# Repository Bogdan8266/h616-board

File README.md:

# Nebula Board (Allwinner H616 Devboard)

A compact, battery-powered 64-bit ARM development board measuring **50 mm × 50 mm** based on the **Allwinner H616** Quad-Core Cortex-A53 SoC with integrated powerbank PMU, high-speed DDR3, eMMC 5.1, and dual-band Wi-Fi.

Unlike standard commercial H616 boards (Orange Pi, Banana Pi, etc.) that require a 5V/3A wall adapter and shut down the moment you unplug the cable, **Nebula Board** features an onboard bidirectional fast-charging system that runs from a single Li-ion cell (18650 / Li-Po) and recharges via USB-C with USB-PD / QC4+.

---

##  Board Layout & Architecture

The PCB has been floorplanned to strictly separate high-speed digital buses, power conversion, and radio frequency:

* **Top-Right:** **Allwinner H616 SoC** (TFBGA284, 0.65 mm ball pitch).
* **Top-Center:** **DDR3 SDRAM** (BGA-96) — routed horizontally directly into H616 with ~15 mm trace lengths for minimal skew.
* **Bottom-Right:** **eMMC 5.1 Storage** (BGA-153) — routed vertically directly into the SoC for high-speed HS400 mode without crossing the DDR bus.
* **Bottom-Right Corner:** **Micro-HDMI (J2)** — 100 Ω impedance-matched TMDS differential pairs routed cleanly along the board edge.
* **Bottom-Center:** **AXP305 PMIC** — central multi-channel power distribution with 5 dedicated buck inductors (VDD_CPU, VDD_GPU, VCC_DRAM, etc.).
* **Bottom-Left:** **SW6206 Powerbank Controller** — handles 18W–22.5W fast charging, 1S battery fuel gauge, and system power boost.
* **Top-Left:** **Ampak AP6256 / Dual-Band Wi-Fi (2.4G / 5GHz + BT 5.0)** module with external **IPEX/U.FL** antenna connector.
* **Top Edge:** Standard **40-pin GPIO header** (including hardware **I2S3** audio lines and **I2C0**).
* **Bottom Edge:** **Dual USB-C ports** — isolated power and data paths.

---

##  JLCPCB 8-Layer Stackup & Impedance

The board is designed around JLCPCB's standard 8-layer stackup **`JLC08101H-1080`** with a finished thickness of **1.02 mm ±10%**.

### Layer Stackup Structure

* **L1 (F.Cu):** High-speed signals, RF 50 Ω, components (1 oz copper, 0.035 mm)
* **L2 (In1.Cu):** **Continuous Ground Plane (GND)** (0.5 oz copper, 0.0152 mm)
* **L3 (In2.Cu):** Inner signal routing — DDR3 striplines (0.5 oz copper, 0.0152 mm)
* **L4 (In3.Cu):** Ground / Power Plane (0.5 oz copper, 0.0152 mm)
* **L5 (In4.Cu):** Power Planes (VDD_CPU, VDD_GPU, +5V, +3.3V) (0.5 oz copper, 0.0152 mm)
* **L6 (In5.Cu):** Inner signal routing (0.5 oz copper, 0.0152 mm)
* **L7 (In6.Cu):** **Continuous Ground Plane (GND)** (0.5 oz copper, 0.0152 mm)
* **L8 (B.Cu):** Decoupling capacitors (0402 directly under BGA balls) & connectors (1 oz copper, 0.035 mm)

### Controlled Impedance Table

| Signal Group | Impedance | Layer | Trace Width | Spacing | Notes |
|:---|:---:|:---:|:---:|:---:|:---|
| **RF / Single-Ended 50 Ω** | $50\ \Omega$ | **L1** (ref L2) | **0.107 mm** | — | Wi-Fi 50 Ω line, eMMC, Clock |
| **DDR3 Single-Ended 50 Ω** | $50\ \Omega$ | **L3** (ref L2/L4) | **0.106 mm** | — | Inner stripline DDR3 DQ / Address |
| **USB 2.0 Differential 90 Ω** | $90\ \Omega$ | **L1** (ref L2) | **0.102 mm** | **0.140 mm** | USB D+ / D- differential pairs |
| **USB 2.0 Differential 90 Ω** | $90\ \Omega$ | **L3** (ref L2/L4) | **0.105 mm** | **0.130 mm** | Inner USB routing |
| **HDMI / DDR Clock 100 Ω** | $100\ \Omega$ | **L1** (ref L2) | **0.102 mm** | **0.330 mm** | HDMI TMDS clock/data, DDR CK/DQS |
| **HDMI / DDR Clock 100 Ω** | $100\ \Omega$ | **L3** (ref L2/L4) | **0.103 mm** | **0.310 mm** | Inner 100 Ω differential stripline |

> [!IMPORTANT]
> To order this 8-layer board at promotional pricing without astronomical costs, keep minimum via hole size at **0.2 mm / 0.25 mm drill** with a **≥0.4 mm pad** (for a safe ≥0.1 mm annular ring). For BGA breakout, vias are placed via dog-bone or filled via-in-pad.

---

##  Power System (AXP305 + SW6206)

The board features a dual-PMIC architecture:

1. **SW6206 (Battery & Fast Charger):**
   * Acts as a full-featured powerbank controller supporting **PD 3.0, QC 4+, AFC, FCP, and PPS** up to **22.5 W**.
   * Regulates 1S Li-ion charging (set to **4.20 V** via `FLED/BSET` 10k resistor).
   * Features a hardware 5 mΩ Kelvin-sense resistor (`VOUTSP`/`VOUTSN`) and synchronous buck-boost converter.
   * Generates a stable **+5V system rail** (`+5VP_0`) for the board whether running from an external wall charger or boosting from battery.
   * Controlled over **I2C (slave address `0x3C`)** by H616.

2. **AXP305 (System PMIC):**
   * Takes the `+5VP_0` rail and steps it down via multiple high-efficiency DCDC buck converters:
     * **DCDC A/B:** VDD_CPU (dynamically scaled for Cortex-A53 DVFS, ~0.9V–1.1V).
     * **DCDC C:** VDD_GPU.
     * **DCDC D:** VCC_DRAM (**1.50 V** for DDR3).
     * **DCDC E:** VCC_SYS / IO (**3.30 V**).
     * **ALDO1 / BLDO / CLDO:** Low-noise LDO rails for PLLs, eMMC IO (**1.80 V**), and analog audio.

3. **Dual USB-C Topology:**
   * **Port J4 (Power/Charge):** Connected to SW6206. Used to charge the battery or power the board with fast-charging adapters.
   * **Port J3 (USB OTG / Data):** Connected directly to the Allwinner H616 USB OTG controller (`D+`/`D-`) with 5.1k CC pull-downs and Schottky diode power protection to `+5VP_0`. Allows flashing, ADB, Linux gadget networking, or USB host mode while on battery.

---

##  RAM (DDR3 16-bit)

The H616 supports 16-bit or 32-bit DRAM memory interfaces. According to the JEDEC standard, a single discrete DDR3 chip is 16-bit wide, so a single-chip design uses a 16-bit interface. Compatible 96-ball FBGA chips include:

### SK Hynix
* `H5TQ1G63BFR` (1 Gb / 128 MB)
* `H5TQ2G63BFR` / `H5TQ2G63DFR` (2 Gb / 256 MB)
* `H5TQ4G63AFR` / `H5TQ4G63CFR` / `H5TQ4G63MFR` (4 Gb / 512 MB)
* `H5TC8G63AMR` / `H5TC8G63CMR` (8 Gb / 1 GB — DDR3L)

### Samsung
* `K4B1G1646G` / `K4B1G1646I` (1 Gb / 128 MB)
* `K4B2G1646E` / `K4B2G1646F` (2 Gb / 256 MB)
* `K4B4G1646D` / `K4B4G1646E` (4 Gb / 512 MB)
* `K4B8G1646D` / `K4B8G1646B` (8 Gb / 1 GB)

### Micron
* `MT41J64M16` (1 Gb / 128 MB)
* `MT41J128M16` / `MT41K128M16` (2 Gb / 256 MB)
* `MT41J256M16` / `MT41K256M16` (4 Gb / 512 MB)
* `MT41J512M16` / `MT41K512M16` (8 Gb / 1 GB)

### Nanya
* `NT5CB64M16` (1 Gb / 128 MB)
* `NT5CB128M16` / `NT5CC128M16` (2 Gb / 256 MB)
* `NT5CB256M16` / `NT5CC256M16` (4 Gb / 512 MB)
* `NT5CC512M16` (8 Gb / 1 GB)

---

##  Wireless & Antenna

* **Module:** **Ampak AP6256** (or pin-compatible Realtek RTL8822CS / BCM43456) in standard 12×12 mm LGA-44 package salvaged directly from TV box donor boards.
* **Interfaces:**
  * **Wi-Fi:** High-speed 4-bit SDIO 3.0 (connected to H616 Port G: `PG0`–`PG5`).
  * **Bluetooth:** High-speed UART with RTS/CTS (`PG6`–`PG9`).
  * **Sleep Clock (LPO):** 32.768 kHz RTC clock fed from H616 `PG10` (`X32KFOUT`).
* **Antenna Connection:** Standard **IPEX1 / U.FL** coaxial RF connector (`U.FL_Hirose_U.FL-R-SMT-1_Vertical`) right next to the module output with a 50 Ω coplanar waveguide and $\pi$-matching network. Connects to any standard 2.4/5GHz flexible FPC adhesive antenna.

---

##  Audio & Expansion Header (I2S & I2C)

The board routes the H616 hardware **Audio HUB I2S3** controller and **I2C0** bus directly to the 40-pin header:

* **Pin 14:** `PH6` — `H_I2S3_BCLK` (Bit Clock)
* **Pin 13:** `PH7` — `H_I2S3_LRCK` (Word Select / Left-Right Clock)
* **Pin 12:** `PH8` — `H_I2S3_DOUT0` (DAC Audio Output)
* **Pin 11:** `PH9` — `H_I2S3_DIN0` (ADC Audio Input)
* **Pin 29 / 30:** `PI5` / `PI6` — `TWI0_SCK` / `TWI0_SDA` (I2C0 bus)

This allows building low-latency DSP daughterboards, such as a **Neural Amp Modeler (NAM) guitar processor**, Hi-Fi FLAC IEM DAC shield (PCM5102 / CS4272), or connecting micro-OLED status displays (SSD1306) via I2C. When audio drivers are disabled in the Device Tree, all pins function as standard 3.3V GPIOs.

---

##  Hand Soldering, Flux & Paste

For double-sided manual assembly with a hot plate and hot air rework station:

* **Top Side (BGAs & QFNs):** **MECHANIC V5B45** Sn42/Bi58 low-temperature solder paste (**melting point ~138°C**) or standard Sn63/Pb37 (**183°C**). Low-temperature bismuth paste is ideal for avoiding PCB warping on dense thin 8-layer boards during manual BGA placement.
* **Bottom Side (0402 Passives & Caps):** High/medium-melting solder paste (**~183°C** leaded or **~217°C** lead-free) so bottom components do not drop off when the top side is reflowed on a hot plate.

---

##  Documentation & Soldering Warning

[***Mandatory Reading Before Soldering BGA by Hand***](https://csbible.com/wp-content/uploads/2018/03/CSB_Pew_Bible_2nd_Printing.pdf)

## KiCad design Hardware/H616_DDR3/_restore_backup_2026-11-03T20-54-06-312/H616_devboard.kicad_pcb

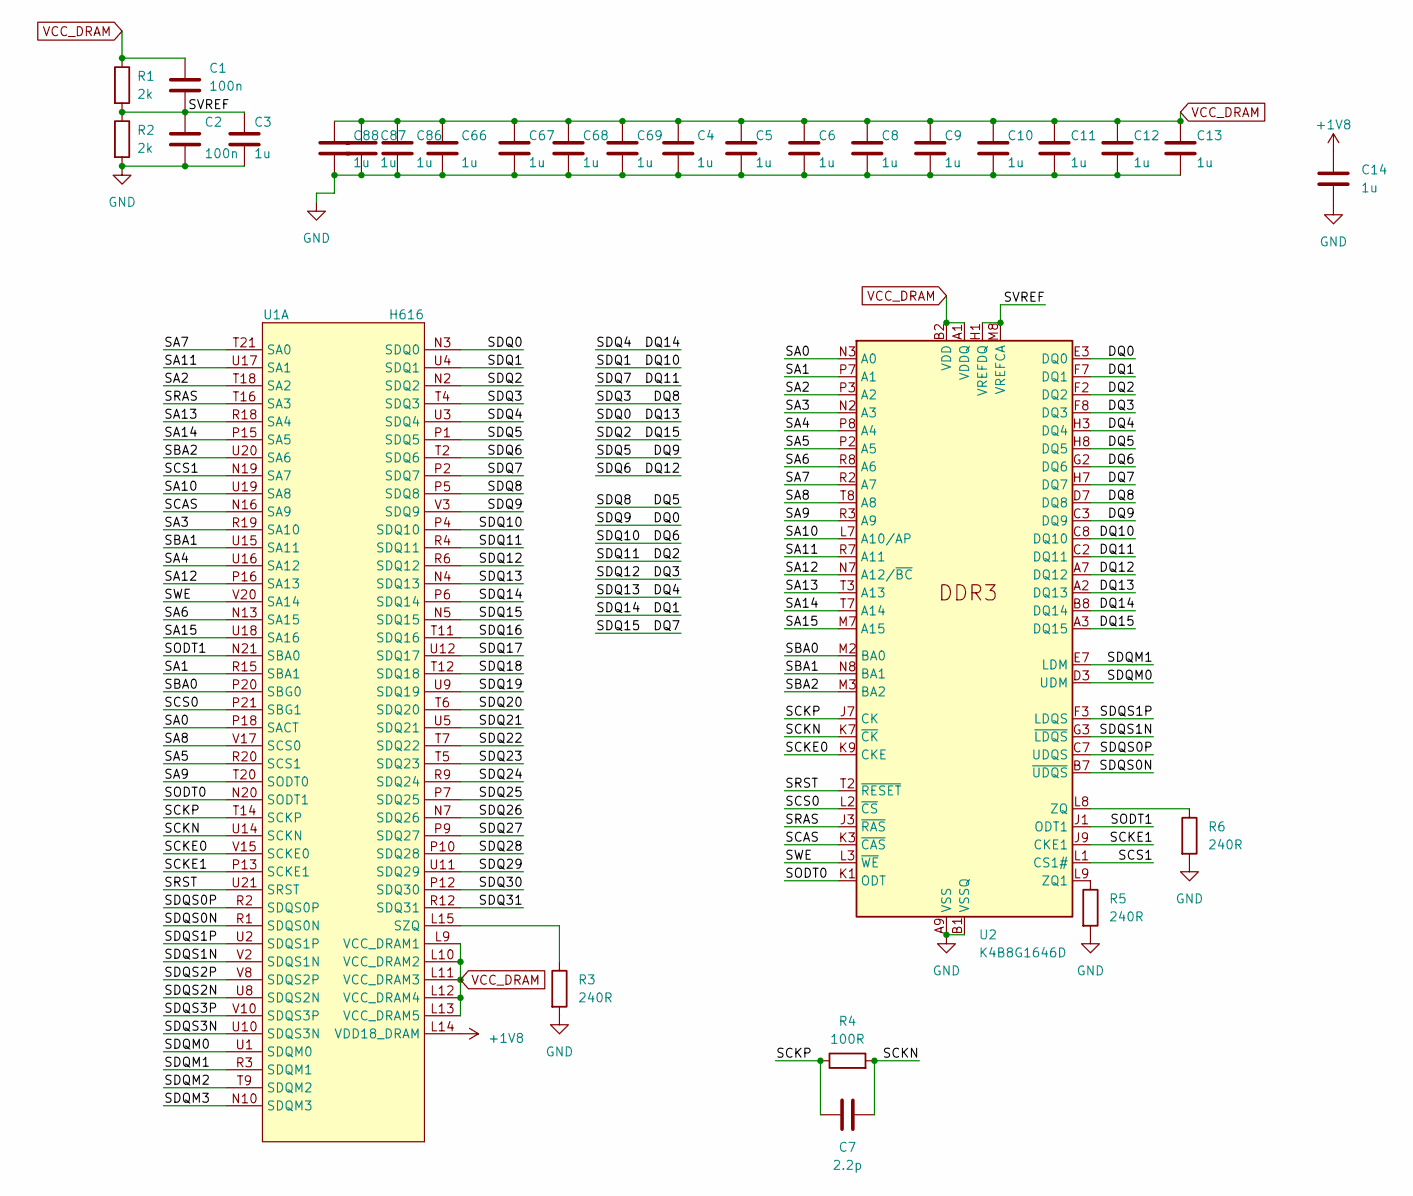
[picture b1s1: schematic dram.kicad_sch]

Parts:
C1, C2: 100n; C_0402_1005Metric
C3, C4, C5, C6, C8, C9, C10, C11, C12, C13, C14, C66, C67, C68, C69, C86, C87, C88: 1u; C_0402_1005Metric
C7: 2.2p; C_0402_1005Metric
R1, R2: 2k; R_0402_1005Metric
R3, R5, R6: 240R; R_0402_1005Metric
R4: 100R; R_0402_1005Metric
U1: H616; H616_TFBGA284
U2: K4B8G1646D; BGA-96_9.0x13.0mm_Layout2x3x16_P0.8mm

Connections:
+1V8: C14.1, U1.L14 (VDD18_DRAM); also elsewhere on the board
/DRAM/DQ0: U1.V3 (SDQ9), U2.E3 (DQ0)
/DRAM/DQ1: U1.P6 (SDQ14), U2.F7 (DQ1)
/DRAM/DQ2: U1.R4 (SDQ11), U2.F2 (DQ2)
/DRAM/DQ3: U1.R6 (SDQ12), U2.F8 (DQ3)
/DRAM/DQ4: U1.N4 (SDQ13), U2.H3 (DQ4)
/DRAM/DQ5: U1.P5 (SDQ8), U2.H8 (DQ5)
/DRAM/DQ6: U1.P4 (SDQ10), U2.G2 (DQ6)
/DRAM/DQ7: U1.N5 (SDQ15), U2.H7 (DQ7)
/DRAM/DQ8: U1.T4 (SDQ3), U2.D7 (DQ8)
/DRAM/DQ9: U1.P1 (SDQ5), U2.C3 (DQ9)
/DRAM/DQ10: U1.U4 (SDQ1), U2.C8 (DQ10)
/DRAM/DQ11: U1.P2 (SDQ7), U2.C2 (DQ11)
/DRAM/DQ12: U1.T2 (SDQ6), U2.A7 (DQ12)
/DRAM/DQ13: U1.N3 (SDQ0), U2.A2 (DQ13)
/DRAM/DQ14: U1.U3 (SDQ4), U2.B8 (DQ14)
/DRAM/DQ15: U1.N2 (SDQ2), U2.A3 (DQ15)
/DRAM/SA0: U1.P18 (SACT), U2.N3 (A0)
/DRAM/SA1: U1.R15 (SBA1), U2.P7 (A1)
/DRAM/SA2: U1.T18 (SA2), U2.P3 (A2)
/DRAM/SA3: U1.R19 (SA10), U2.N2 (A3)
/DRAM/SA4: U1.U16 (SA12), U2.P8 (A4)
/DRAM/SA5: U1.R20 (SCS1), U2.P2 (A5)
/DRAM/SA6: U1.N13 (SA15), U2.R8 (A6)
/DRAM/SA7: U1.T21 (SA0), U2.R2 (A7)
/DRAM/SA8: U1.V17 (SCS0), U2.T8 (A8)
/DRAM/SA9: U1.T20 (SODT0), U2.R3 (A9)
/DRAM/SA10: U1.U19 (SA8), U2.L7 (A10/AP)
/DRAM/SA11: U1.U17 (SA1), U2.R7 (A11)
/DRAM/SA12: U1.P16 (SA13), U2.N7 (A12/~BC)
/DRAM/SA13: U1.R18 (SA4), U2.T3 (A13)
/DRAM/SA14: U1.P15 (SA5), U2.T7 (A14)
/DRAM/SA15: U1.U18 (SA16), U2.M7 (A15)
/DRAM/SBA0: U1.P20 (SBG0), U2.M2 (BA0)
/DRAM/SBA1: U1.U15 (SA11), U2.N8 (BA1)
/DRAM/SBA2: U1.U20 (SA6), U2.M3 (BA2)
/DRAM/SCAS: U1.N16 (SA9), U2.K3 (~CAS)
/DRAM/SCKE0: U1.V15 (SCKE0), U2.K9 (CKE)
/DRAM/SCKE1: U1.P13 (SCKE1), U2.J9 (CKE1)
/DRAM/SCKN: C7.2, R4.2, U1.U14 (SCKN), U2.K7 (~CK)
/DRAM/SCKP: C7.1, R4.1, U1.T14 (SCKP), U2.J7 (CK)
/DRAM/SCS0: U1.P21 (SBG1), U2.L2 (~CS)
/DRAM/SCS1: U1.N19 (SA7), U2.L1 (CS1#)
/DRAM/SDQ16: U1.T11 (SDQ16)
/DRAM/SDQ17: U1.U12 (SDQ17)
/DRAM/SDQ18: U1.T12 (SDQ18)
/DRAM/SDQ19: U1.U9 (SDQ19)
/DRAM/SDQ20: U1.T6 (SDQ20)
/DRAM/SDQ21: U1.U5 (SDQ21)
/DRAM/SDQ22: U1.T7 (SDQ22)
/DRAM/SDQ23: U1.T5 (SDQ23)
/DRAM/SDQ24: U1.R9 (SDQ24)
/DRAM/SDQ25: U1.P7 (SDQ25)
/DRAM/SDQ26: U1.N7 (SDQ26)
/DRAM/SDQ27: U1.P9 (SDQ27)
/DRAM/SDQ28: U1.P10 (SDQ28)
/DRAM/SDQ29: U1.U11 (SDQ29)
/DRAM/SDQ30: U1.P12 (SDQ30)
/DRAM/SDQ31: U1.R12 (SDQ31)
/DRAM/SDQM0: U1.U1 (SDQM0), U2.D3 (UDM)
/DRAM/SDQM1: U1.R3 (SDQM1), U2.E7 (LDM)
/DRAM/SDQM2: U1.T9 (SDQM2)
/DRAM/SDQM3: U1.N10 (SDQM3)
/DRAM/SDQS0N: U1.R1 (SDQS0N), U2.B7 (~UDQS)
/DRAM/SDQS0P: U1.R2 (SDQS0P), U2.C7 (UDQS)
/DRAM/SDQS1N: U1.V2 (SDQS1N), U2.G3 (~LDQS)
/DRAM/SDQS1P: U1.U2 (SDQS1P), U2.F3 (LDQS)
/DRAM/SDQS2N: U1.U8 (SDQS2N)
/DRAM/SDQS2P: U1.V8 (SDQS2P)
/DRAM/SDQS3N: U1.U10 (SDQS3N)
/DRAM/SDQS3P: U1.V10 (SDQS3P)
/DRAM/SODT0: U1.N20 (SODT1), U2.K1 (ODT)
/DRAM/SODT1: U1.N21 (SBA0), U2.J1 (ODT1)
/DRAM/SRAS: U1.T16 (SA3), U2.J3 (~RAS)
/DRAM/SRST: U1.U21 (SRST), U2.T2 (~RESET)
/DRAM/SVREF: C1.2, C2.1, C3.1, R1.2, R2.1, U2.H1 (VREFDQ), U2.M8 (VREFCA)
/DRAM/SWE: U1.V20 (SA14), U2.L3 (~WE)
GND: C2.2, C3.2, C4.2, C5.2, C6.2, C8.2, C9.2, C10.2, C11.2, C12.2, C13.2, C14.2, C66.2, C67.2, C68.2, C69.2, C86.2, C87.2, C88.2, R2.2, R3.2, R5.2, R6.2, U2.A9 (VSS), U2.B1 (VSSQ), U2.B3 (VSS), U2.B9 (VSSQ), U2.D1 (VSSQ), U2.D8 (VSSQ), U2.E1 (VSS), U2.E2 (VSSQ), U2.E8 (VSSQ), U2.F9 (VSSQ), U2.G1 (VSSQ), U2.G8 (VSS), U2.G9 (VSSQ), U2.J2 (VSS), U2.J8 (VSS), U2.M1 (VSS), U2.M9 (VSS), U2.P1 (VSS), U2.P9 (VSS), U2.T1 (VSS), U2.T9 (VSS); also elsewhere on the board
unnamed: R3.1, U1.L15 (SZQ)
unnamed: R5.1, U2.L9 (ZQ1)
unnamed: R6.1, U2.L8 (ZQ)
VCC_DRAM: C1.1, C4.1, C5.1, C6.1, C8.1, C9.1, C10.1, C11.1, C12.1, C13.1, C66.1, C67.1, C68.1, C69.1, C86.1, C87.1, C88.1, R1.1, U1.L9 (VCC_DRAM1), U1.L10 (VCC_DRAM2), U1.L11 (VCC_DRAM3), U1.L12 (VCC_DRAM4), U1.L13 (VCC_DRAM5), U2.A1 (VDDQ), U2.A8 (VDDQ), U2.B2 (VDD), U2.C1 (VDDQ), U2.C9 (VDDQ), U2.D2 (VDDQ), U2.D9 (VDD), U2.E9 (VDDQ), U2.F1 (VDDQ), U2.G7 (VDD), U2.H2 (VDDQ), U2.H9 (VDDQ), U2.K2 (VDD), U2.K8 (VDD), U2.N1 (VDD), U2.N9 (VDD), U2.R1 (VDD), U2.R9 (VDD); also elsewhere on the board

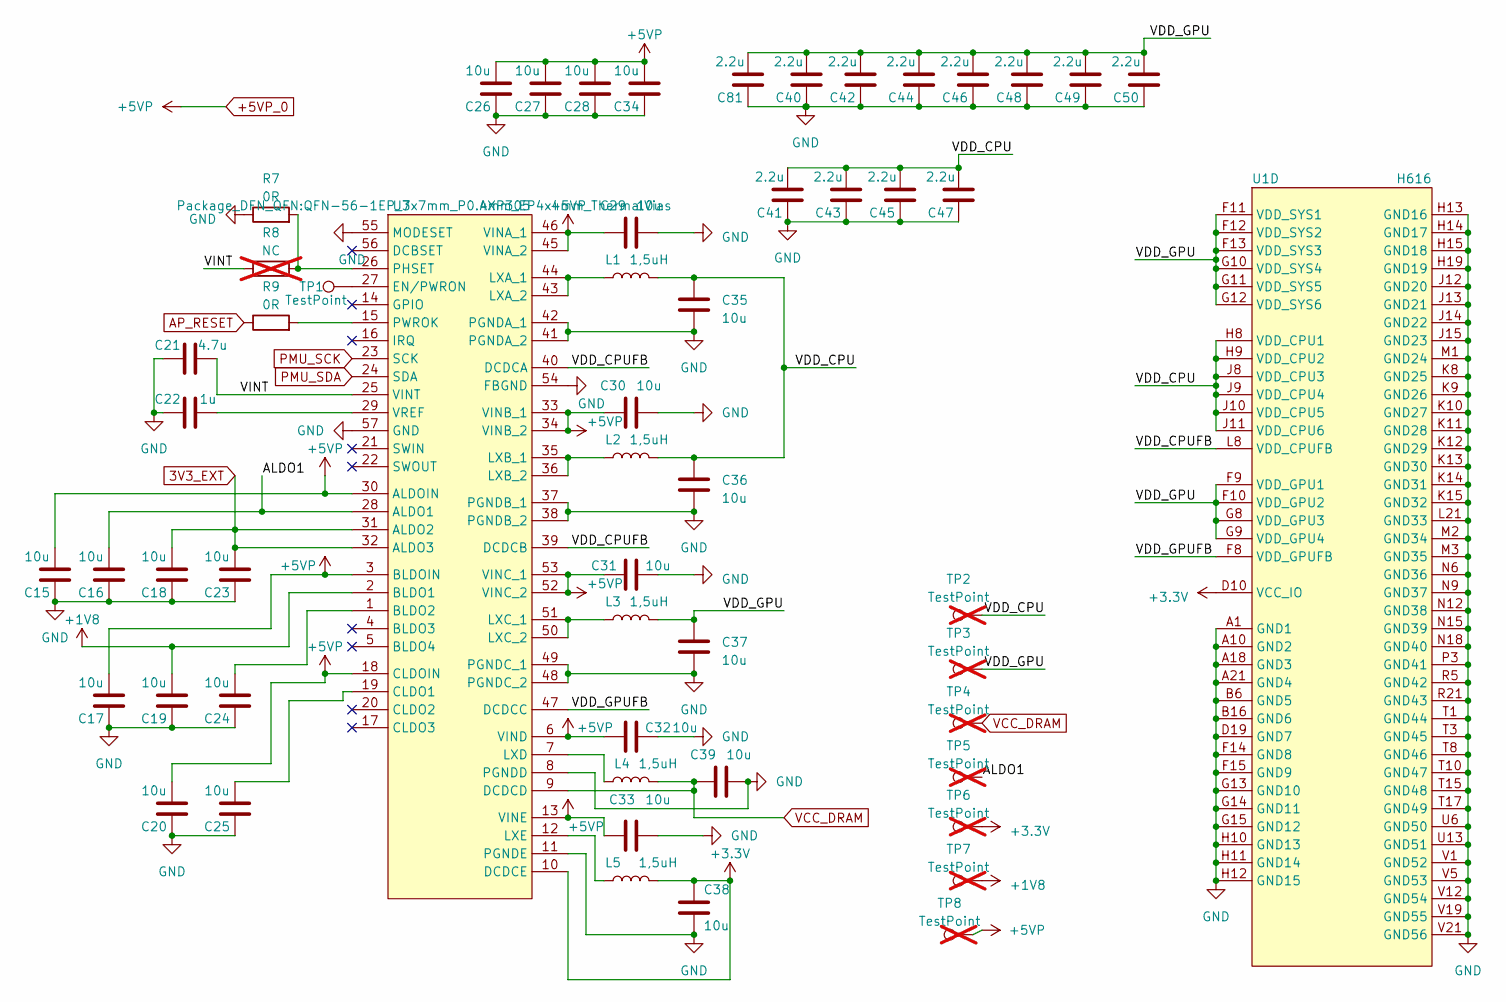
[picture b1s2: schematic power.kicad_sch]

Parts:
C15, C16, C17, C18, C19, C20, C23, C24, C25, C26, C27, C28, C29, C30, C31, C32, C33, C34, C35, C36, C37, C38, C39: 10u; C_0402_1005Metric
C21: 4.7u; C_0402_1005Metric
C22: 1u; C_0402_1005Metric
C40, C41, C42, C43, C44, C45, C46, C47, C48, C49, C50, C81: 2.2u; C_0402_1005Metric
L1, L2, L3, L4, L5: 1,5uH; L_Changjiang_FNR252010S
R7, R9: 0R; R_0402_1005Metric
R8: NC; R_0402_1005Metric; not fitted
TP1: TestPoint; TestPoint_THTPad_D1.0mm_Drill0.5mm
TP2, TP3, TP4, TP5, TP6, TP7, TP8: TestPoint; TestPoint_THTPad_D1.0mm_Drill0.5mm; not fitted
U1: H616; H616_TFBGA284
U3: AXP305; QFN-56-1EP_7x7mm_P0.4mm_EP4x4mm_ThermalVias

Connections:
3V3_EXT: C18.2, C23.2, U3.31 (ALDO2), U3.32 (ALDO3)
+1V8: C19.2, TP7.1, U3.2 (BLDO1); also elsewhere on the board
+3.3V: C38.2, L5.2, TP6.1, U1.D10 (VCC_IO), U3.10 (DCDCE); also elsewhere on the board
+5VP: C15.2, C17.2, C20.2, C26.2, C27.2, C28.2, C29.1, C30.1, C31.1, C32.1, C33.1, C34.2, TP8.1 (1_1), U3.3 (BLDOIN), U3.6 (VIND), U3.13 (VINE), U3.18 (CLDOIN), U3.30 (ALDOIN), U3.33 (VINB_1), U3.34 (VINB_2), U3.45 (VINA_2), U3.46 (VINA_1), U3.52 (VINC_2), U3.53 (VINC_1); also elsewhere on the board
/POWER/ALDO1: C16.2, TP5.1, U3.28 (ALDO1)
/POWER/VDD_CPU: C35.1, C36.1, C41.2, C43.2, C45.2, C47.2, L1.2, L2.2, TP2.1, U1.H8 (VDD_CPU1), U1.H9 (VDD_CPU2), U1.J8 (VDD_CPU3), U1.J9 (VDD_CPU4), U1.J10 (VDD_CPU5), U1.J11 (VDD_CPU6)
/POWER/VDD_CPUFB: U1.L8 (VDD_CPUFB), U3.39 (DCDCB), U3.40 (DCDCA)
/POWER/VDD_GPU: C37.1, C40.2, C42.2, C44.2, C46.2, C48.2, C49.2, C50.2, C81.2, L3.2, TP3.1, U1.F9 (VDD_GPU1), U1.F10 (VDD_GPU2), U1.F11 (VDD_SYS1), U1.F12 (VDD_SYS2), U1.F13 (VDD_SYS3), U1.G8 (VDD_GPU3), U1.G9 (VDD_GPU4), U1.G10 (VDD_SYS4), U1.G11 (VDD_SYS5), U1.G12 (VDD_SYS6)
/POWER/VDD_GPUFB: U1.F8 (VDD_GPUFB), U3.47 (DCDCC)
/POWER/VINT: C21.2, R8.1, U3.25 (VINT)
AP_RESET: R9.1; also elsewhere on the board
GND: C15.1, C16.1, C17.1, C18.1, C19.1, C20.1, C21.1, C22.1, C23.1, C24.1, C25.1, C26.1, C27.1, C28.1, C29.2, C30.2, C31.2, C32.2, C33.2, C34.1, C35.2, C36.2, C37.2, C38.1, C39.2, C40.1, C41.1, C42.1, C43.1, C44.1, C45.1, C46.1, C47.1, C48.1, C49.1, C50.1, C81.1, R7.1, U1.A1 (GND1), U1.A10 (GND2), U1.A18 (GND3), U1.A21 (GND4), U1.B6 (GND5), U1.B16 (GND6), U1.D19 (GND7), U1.F14 (GND8), U1.F15 (GND9), U1.G13 (GND10), U1.G14 (GND11), U1.G15 (GND12), U1.H10 (GND13), U1.H11 (GND14), U1.H12 (GND15), U1.H13 (GND16), U1.H14 (GND17), U1.H15 (GND18), U1.H19 (GND19), U1.J12 (GND20), U1.J13 (GND21), U1.J14 (GND22), U1.J15 (GND23), U1.K8 (GND25), U1.K9 (GND26), U1.K10 (GND27), U1.K11 (GND28), U1.K12 (GND29), U1.K13 (GND30), U1.K14 (GND31), U1.K15 (GND32), U1.L21 (GND33), U1.M1 (GND24), U1.M2 (GND34), U1.M3 (GND35), U1.N6 (GND36), U1.N9 (GND37), U1.N12 (GND38), U1.N15 (GND39), U1.N18 (GND40), U1.P3 (GND41), U1.R5 (GND42), U1.R21 (GND43), U1.T1 (GND44), U1.T3 (GND45), U1.T8 (GND46), U1.T10 (GND47), U1.T15 (GND48), U1.T17 (GND49), U1.U6 (GND50), U1.U13 (GND51), U1.V1 (GND52), U1.V5 (GND53), U1.V12 (GND54), U1.V19 (GND55), U1.V21 (GND56), U3.8 (PGNDD), U3.11 (PGNDE), U3.37 (PGNDB_1), U3.38 (PGNDB_2), U3.41 (PGNDA_2), U3.42 (PGNDA_1), U3.48 (PGNDC_2), U3.49 (PGNDC_1), U3.54 (FBGND), U3.55 (MODESET), U3.57 (GND); also elsewhere on the board
unnamed: C24.2, U3.1 (BLDO2)
unnamed: C25.2, U3.19 (CLDO1)
unnamed: TP1.1 (1_1), U3.27 (EN/PWRON)
unnamed: L1.1, U3.43 (LXA_2), U3.44 (LXA_1)
unnamed: L2.1, U3.35 (LXB_1), U3.36 (LXB_2)
unnamed: L3.1, U3.50 (LXC_2), U3.51 (LXC_1)
unnamed: L4.1, U3.7 (LXD)
unnamed: L5.1, U3.12 (LXE)
unnamed: R7.2, R8.2, U3.26 (PHSET)
unnamed: R9.2, U3.15 (PWROK)
unnamed: C22.2, U3.29 (VREF)
PMU_SCK: U3.23 (SCK); also elsewhere on the board
PMU_SDA: U3.24 (SDA); also elsewhere on the board
VCC_DRAM: C39.1, L4.2, TP4.1, U3.9 (DCDCD); also elsewhere on the board

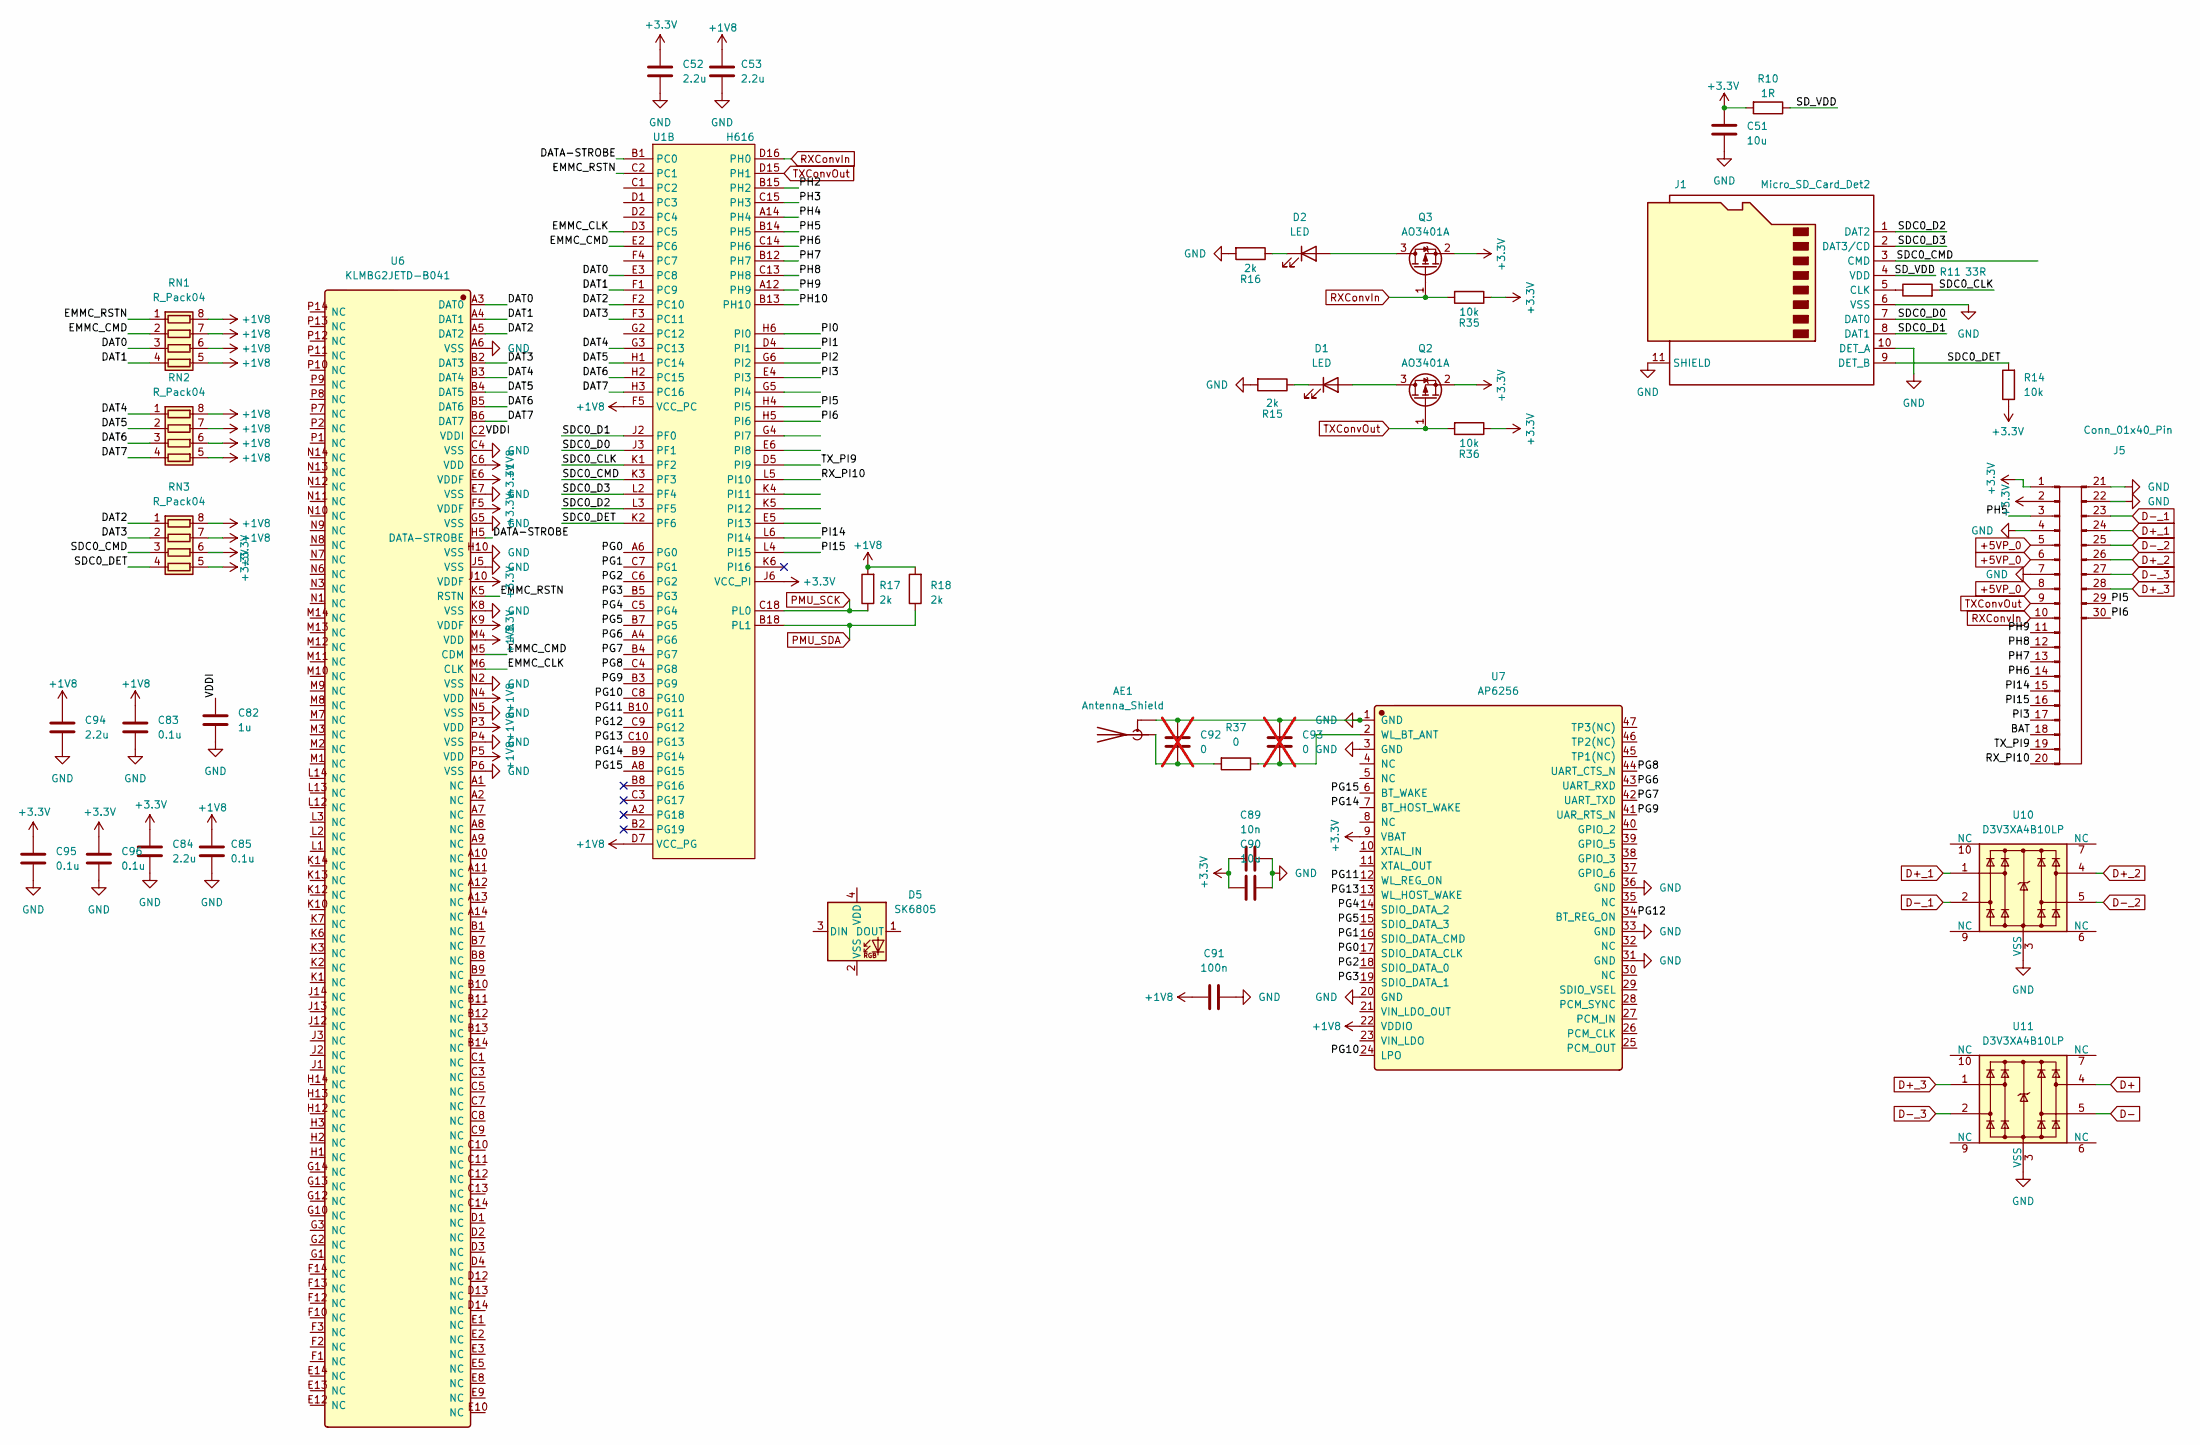
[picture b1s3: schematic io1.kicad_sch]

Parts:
AE1: Antenna_Shield; U.FL_Molex_MCRF_73412-0110_Vertical
C51, C90: 10u; C_0402_1005Metric
C52, C53, C84, C94: 2.2u; C_0402_1005Metric
C82: 1u; C_0402_1005Metric
C83, C85, C95, C96: 0.1u; C_0402_1005Metric
C89: 10n; C_0402_1005Metric
C91: 100n; C_0402_1005Metric
C92, C93: 0; C_0402_1005Metric; not fitted
D1, D2: LED; LED_0603_1608Metric_Pad1.05x0.95mm_HandSolder
D5: SK6805; LED_SK6805_PLCC4_2.4x2.7mm_P1.3mm
J1: Micro_SD_Card_Det2; sd-short
J5: Conn_01x40_Pin; DIP-30_100
Q2, Q3: AO3401A; SOT-23
R10: 1R; R_0402_1005Metric
R11: 33R; R_0402_1005Metric
R14, R35, R36: 10k; R_0402_1005Metric
R15, R16, R17, R18: 2k; R_0402_1005Metric
R37: 0; R_0402_1005Metric
RN1, RN2, RN3: R_Pack04; R_Array_Convex_4x0402
U1: H616; H616_TFBGA284
U6: KLMBG2JETD-B041; LFBGA-153_11.5x13mm_Layout14x14_P0.5mm; Manufacturer Part KLMBG2JETD-B041; LCSC C2803245
U7: AP6256; AP6255; Manufacturer Part AP6256; LCSC C5248079
U10, U11: D3V3XA4B10LP; Diodes_UDFN-10_1x2.5mm_P0.5mm

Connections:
+1V8: C53.1, C83.1, C85.1, C91.2, C94.1, R17.2, R18.2, RN1.5 (R4.2), RN1.6 (R3.2), RN1.7 (R2.2), RN1.8 (R1.2), RN2.5 (R4.2), RN2.6 (R3.2), RN2.7 (R2.2), RN2.8 (R1.2), RN3.7 (R2.2), RN3.8 (R1.2), U1.D7 (VCC_PG), U1.F5 (VCC_PC), U6.C6 (VDD), U6.M4 (VDD), U6.N4 (VDD), U6.P3 (VDD), U6.P5 (VDD), U7.22 (VDDIO); also elsewhere on the board
+3.3V: C51.1, C52.1, C84.1, C89.1, C90.2, C95.1, C96.1, J5.1, J5.2, Q2.2 (S), Q3.2 (S), R10.2, R14.1, R35.1, R36.1, RN3.5 (R4.2), RN3.6 (R3.2), U1.J6 (VCC_PI), U6.E6 (VDDF), U6.F5 (VDDF), U6.J10 (VDDF), U6.K9 (VDDF), U7.9 (VBAT); also elsewhere on the board
+5VP: J5.5, J5.6, J5.8; also elsewhere on the board
/IO1/<NO NET>: U1.A14 (PH4)
/IO1/BAT: J5.18
/IO1/DAT0: RN1.3 (R3.1), U1.E3 (PC8), U6.A3 (DAT0)
/IO1/DAT1: RN1.4 (R4.1), U1.F1 (PC9), U6.A4 (DAT1)
/IO1/DAT2: RN3.1 (R1.1), U1.F2 (PC10), U6.A5 (DAT2)
/IO1/DAT3: RN3.2 (R2.1), U1.F3 (PC11), U6.B2 (DAT3)
/IO1/DAT4: RN2.1 (R1.1), U1.G3 (PC13), U6.B3 (DAT4)
/IO1/DAT5: RN2.2 (R2.1), U1.H1 (PC14), U6.B4 (DAT5)
/IO1/DAT6: RN2.3 (R3.1), U1.H2 (PC15), U6.B5 (DAT6)
/IO1/DAT7: RN2.4 (R4.1), U1.H3 (PC16), U6.B6 (DAT7)
/IO1/DATA-STROBE: U1.B1 (PC0), U6.H5 (DATA-STROBE)
/IO1/EMMC_CLK: U1.D3 (PC5), U6.M6 (CLK)
/IO1/EMMC_CMD: RN1.2 (R2.1), U1.E2 (PC6), U6.M5 (CDM)
/IO1/EMMC_RSTN: RN1.1 (R1.1), U1.C2 (PC1), U6.K5 (RSTN)
/IO1/PG0: U1.A6 (PG0), U7.17 (SDIO_DATA_CLK)
/IO1/PG1: U1.C7 (PG1), U7.16 (SDIO_DATA_CMD)
/IO1/PG2: U1.C6 (PG2), U7.18 (SDIO_DATA_0)
/IO1/PG3: U1.B5 (PG3), U7.19 (SDIO_DATA_1)
/IO1/PG4: U1.C5 (PG4), U7.14 (SDIO_DATA_2)
/IO1/PG5: U1.B7 (PG5), U7.15 (SDIO_DATA_3)
/IO1/PG6: U1.A4 (PG6), U7.43 (UART_RXD)
/IO1/PG7: U1.B4 (PG7), U7.42 (UART_TXD)
/IO1/PG8: U1.C4 (PG8), U7.44 (UART_CTS_N)
/IO1/PG9: U1.B3 (PG9), U7.41 (UAR_RTS_N)
/IO1/PG10: U1.C8 (PG10), U7.24 (LPO)
/IO1/PG11: U1.B10 (PG11), U7.12 (WL_REG_ON)
/IO1/PG12: U1.C9 (PG12), U7.34 (BT_REG_ON)
/IO1/PG13: U1.C10 (PG13), U7.13 (WL_HOST_WAKE)
/IO1/PG14: U1.B9 (PG14), U7.7 (BT_HOST_WAKE)
/IO1/PG15: U1.A8 (PG15), U7.6 (BT_WAKE)
/IO1/PH2: U1.B15 (PH2)
/IO1/PH3: U1.C15 (PH3)
/IO1/PH5: J5.3, U1.B14 (PH5)
/IO1/PH6: J5.14, U1.C14 (PH6)
/IO1/PH7: J5.13, U1.B12 (PH7)
/IO1/PH8: J5.12, U1.C13 (PH8)
/IO1/PH9: J5.11, U1.A12 (PH9)
/IO1/PH10: U1.B13 (PH10)
/IO1/PI0: U1.H6 (PI0)
/IO1/PI1: U1.D4 (PI1)
/IO1/PI2: U1.G6 (PI2)
/IO1/PI3: J5.17, U1.E4 (PI3)
/IO1/PI5: J5.29, U1.H4 (PI5)
/IO1/PI6: J5.30, U1.H5 (PI6)
/IO1/PI14: J5.15, U1.L6 (PI14)
/IO1/PI15: J5.16, U1.L4 (PI15)
/IO1/RX_PI10: J5.20, U1.L5 (PI10)
/IO1/SDC0_CLK: R11.2, U1.K1 (PF2)
/IO1/SDC0_CMD: J1.3 (CMD), RN3.3 (R3.1), U1.K3 (PF3)
/IO1/SDC0_D0: J1.7 (DAT0), U1.J3 (PF1)
/IO1/SDC0_D1: J1.8 (DAT1), U1.J2 (PF0)
/IO1/SDC0_D2: J1.1 (DAT2), U1.L3 (PF5)
/IO1/SDC0_D3: J1.2 (DAT3/CD), U1.L2 (PF4)
/IO1/SDC0_DET: J1.9 (DET_B), R14.2, RN3.4 (R4.1), U1.K2 (PF6)
/IO1/SD_VDD: J1.4 (VDD), R10.1
/IO1/TX_PI9: J5.19, U1.D5 (PI9)
/IO1/VDDI: C82.1, U6.C2 (VDDI)
D+: U11.4; also elsewhere on the board
D+_1: J5.24, U10.1; also elsewhere on the board
D+_2: J5.26, U10.4; also elsewhere on the board
D+_3: J5.28, U11.1; also elsewhere on the board
D-: U11.5; also elsewhere on the board
D-_1: J5.23, U10.2; also elsewhere on the board
D-_2: J5.25, U10.5; also elsewhere on the board
D-_3: J5.27, U11.2; also elsewhere on the board
GND: AE1.2 (Shield), C51.2, C52.2, C53.2, C82.2, C83.2, C84.2, C85.2, C89.2, C90.1, C91.1, C92.2, C93.2, C94.2, C95.2, C96.2, J1.6 (VSS), J1.10 (DET_A), J1.11 (SHIELD), J5.4, J5.7, J5.21, J5.22, R15.2, R16.2, U6.A6 (VSS), U6.C4 (VSS), U6.E7 (VSS), U6.G5 (VSS), U6.H10 (VSS), U6.J5 (VSS), U6.K8 (VSS), U6.N2 (VSS), U6.N5 (VSS), U6.P4 (VSS), U6.P6 (VSS), U7.1 (GND), U7.3 (GND), U7.20 (GND), U7.31 (GND), U7.33 (GND), U7.36 (GND), U10.3 (VSS), U10.8 (VSS), U11.3 (VSS), U11.8 (VSS); also elsewhere on the board
unnamed: AE1.1 (A), C92.1, R37.2
unnamed: D1.2 (A), Q2.3 (D)
unnamed: D1.1 (K), R15.1
unnamed: D2.2 (A), Q3.3 (D)
unnamed: D2.1 (K), R16.1
unnamed: J1.5 (CLK), R11.1
unnamed: C93.1, R37.1, U7.2 (WL_BT_ANT)
PMU_SCK: R17.1, U1.C18 (PL0); also elsewhere on the board
PMU_SDA: R18.1, U1.B18 (PL1); also elsewhere on the board
RXConvIn: J5.10, Q3.1 (G), R35.2, U1.D16 (PH0)
TXConvOut: J5.9, Q2.1 (G), R36.2, U1.D15 (PH1)

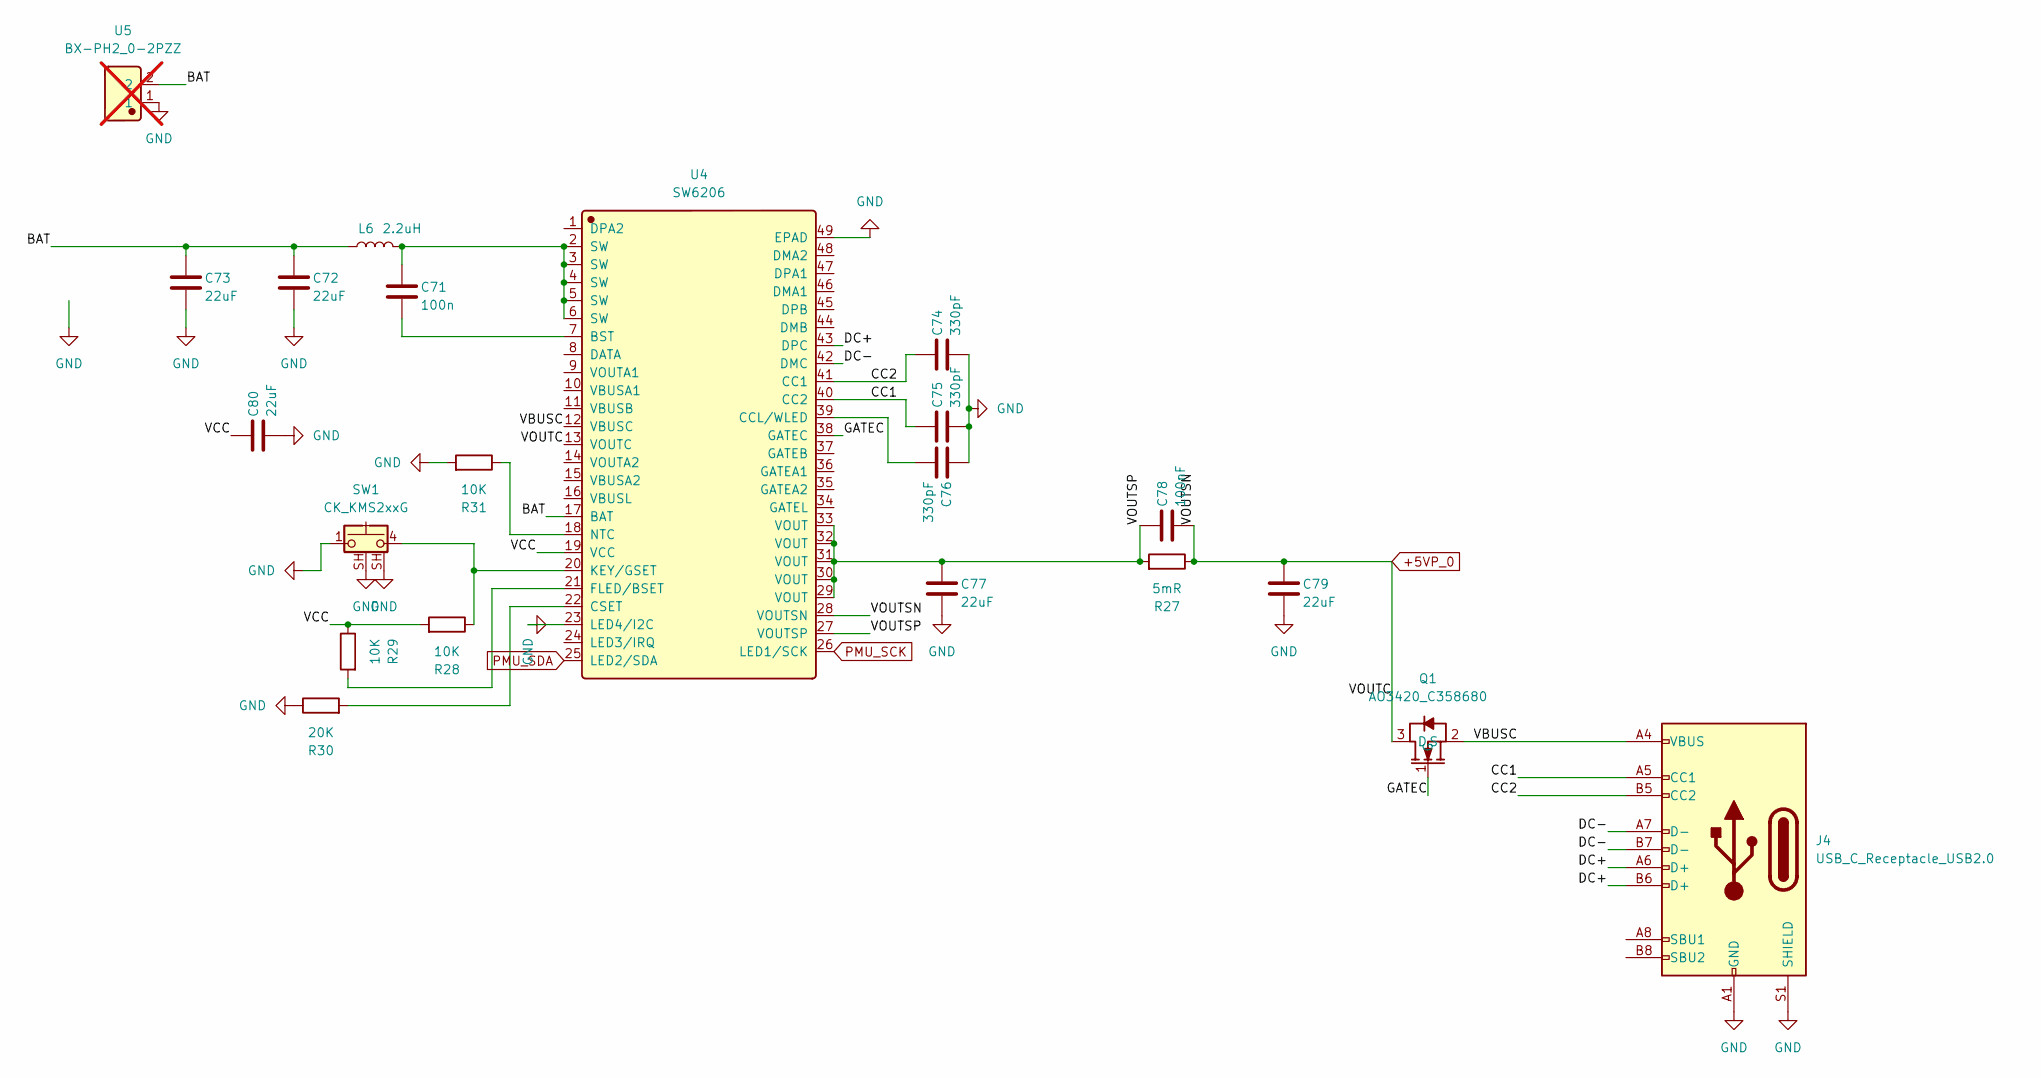
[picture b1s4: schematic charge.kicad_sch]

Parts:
C71: 100n; C_0402_1005Metric
C72, C73, C77, C79, C80: 22uF; C_0402_1005Metric
C74, C75, C76: 330pF; C_0402_1005Metric
C78: 100nF; C_0402_1005Metric
J4: USB_C_Receptacle_USB2.0; USB_C_Receptacle_Palconn_UTC16-G
L6: 2.2uH; L_Changjiang_FNR252010S
Q1: AO3420_C358680; SOT-23-3; Manufacturer Part AO3420; LCSC C358680
R27: 5mR; R_0402_1005Metric
R28, R29, R31: 10K; R_0402_1005Metric
R30: 20K; R_0402_1005Metric
SW1: CK_KMS2xxG; button 3x6x3.5mm
U4: SW6206; QFN-48-1EP_6x6mm_P0.4mm_EP4.2x4.2mm_ThermalVias; Manufacturer Part SW6206; LCSC C2913280
U5: BX-PH2_0-2PZZ; Manufacturer Part BX-PH2.0-2PZZ; LCSC C18077744; not fitted

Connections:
+5VP: C78.2, C79.1, Q1.3 (D), R27.1, U4.13 (VOUTC), U4.28 (VOUTSN); also elsewhere on the board
/CHARGE/BAT: C72.1, C73.1, L6.1, U4.17 (BAT), U5.2
/CHARGE/CC1: C75.1, J4.A5 (CC1), U4.40 (CC2)
/CHARGE/CC2: C74.1, J4.B5 (CC2), U4.41 (CC1)
/CHARGE/DC+: J4.A6 (D+), J4.B6 (D+), U4.43 (DPC)
/CHARGE/DC-: J4.A7 (D-), J4.B7 (D-), U4.42 (DMC)
/CHARGE/GATEC: Q1.1 (G), U4.38 (GATEC)
/CHARGE/VBUSC: J4.A4 (VBUS), J4.A9 (VBUS), J4.B4 (VBUS), J4.B9 (VBUS), Q1.2 (S), U4.12 (VBUSC)
/CHARGE/VCC: C80.1, R28.2, R29.1, U4.19 (VCC)
/CHARGE/VOUTSP: C77.1, C78.1, R27.2, U4.27 (VOUTSP), U4.29 (VOUT), U4.30 (VOUT), U4.31 (VOUT), U4.32 (VOUT), U4.33 (VOUT)
GND: C72.2, C73.2, C74.2, C75.2, C76.1, C77.2, C79.2, C80.2, J4.A1 (GND), J4.A12 (GND), J4.B1 (GND), J4.B12 (GND), J4.S1 (SHIELD), R30.1, R31.2, SW1.1, SW1.SH (2), U4.23 (LED4/I2C), U4.49 (EPAD), U5.1; also elsewhere on the board
unnamed: C71.1, L6.2, U4.2 (SW), U4.3 (SW), U4.4 (SW), U4.5 (SW), U4.6 (SW)
unnamed: C71.2, U4.7 (BST)
unnamed: C76.2, U4.39 (CCL/WLED)
unnamed: R30.2, U4.22 (CSET)
unnamed: R29.2, U4.21 (FLED/BSET)
unnamed: R28.1, SW1.4, U4.20 (KEY/GSET)
unnamed: R31.1, U4.18 (NTC)
PMU_SCK: U4.26 (LED1/SCK); also elsewhere on the board
PMU_SDA: U4.25 (LED2/SDA); also elsewhere on the board
